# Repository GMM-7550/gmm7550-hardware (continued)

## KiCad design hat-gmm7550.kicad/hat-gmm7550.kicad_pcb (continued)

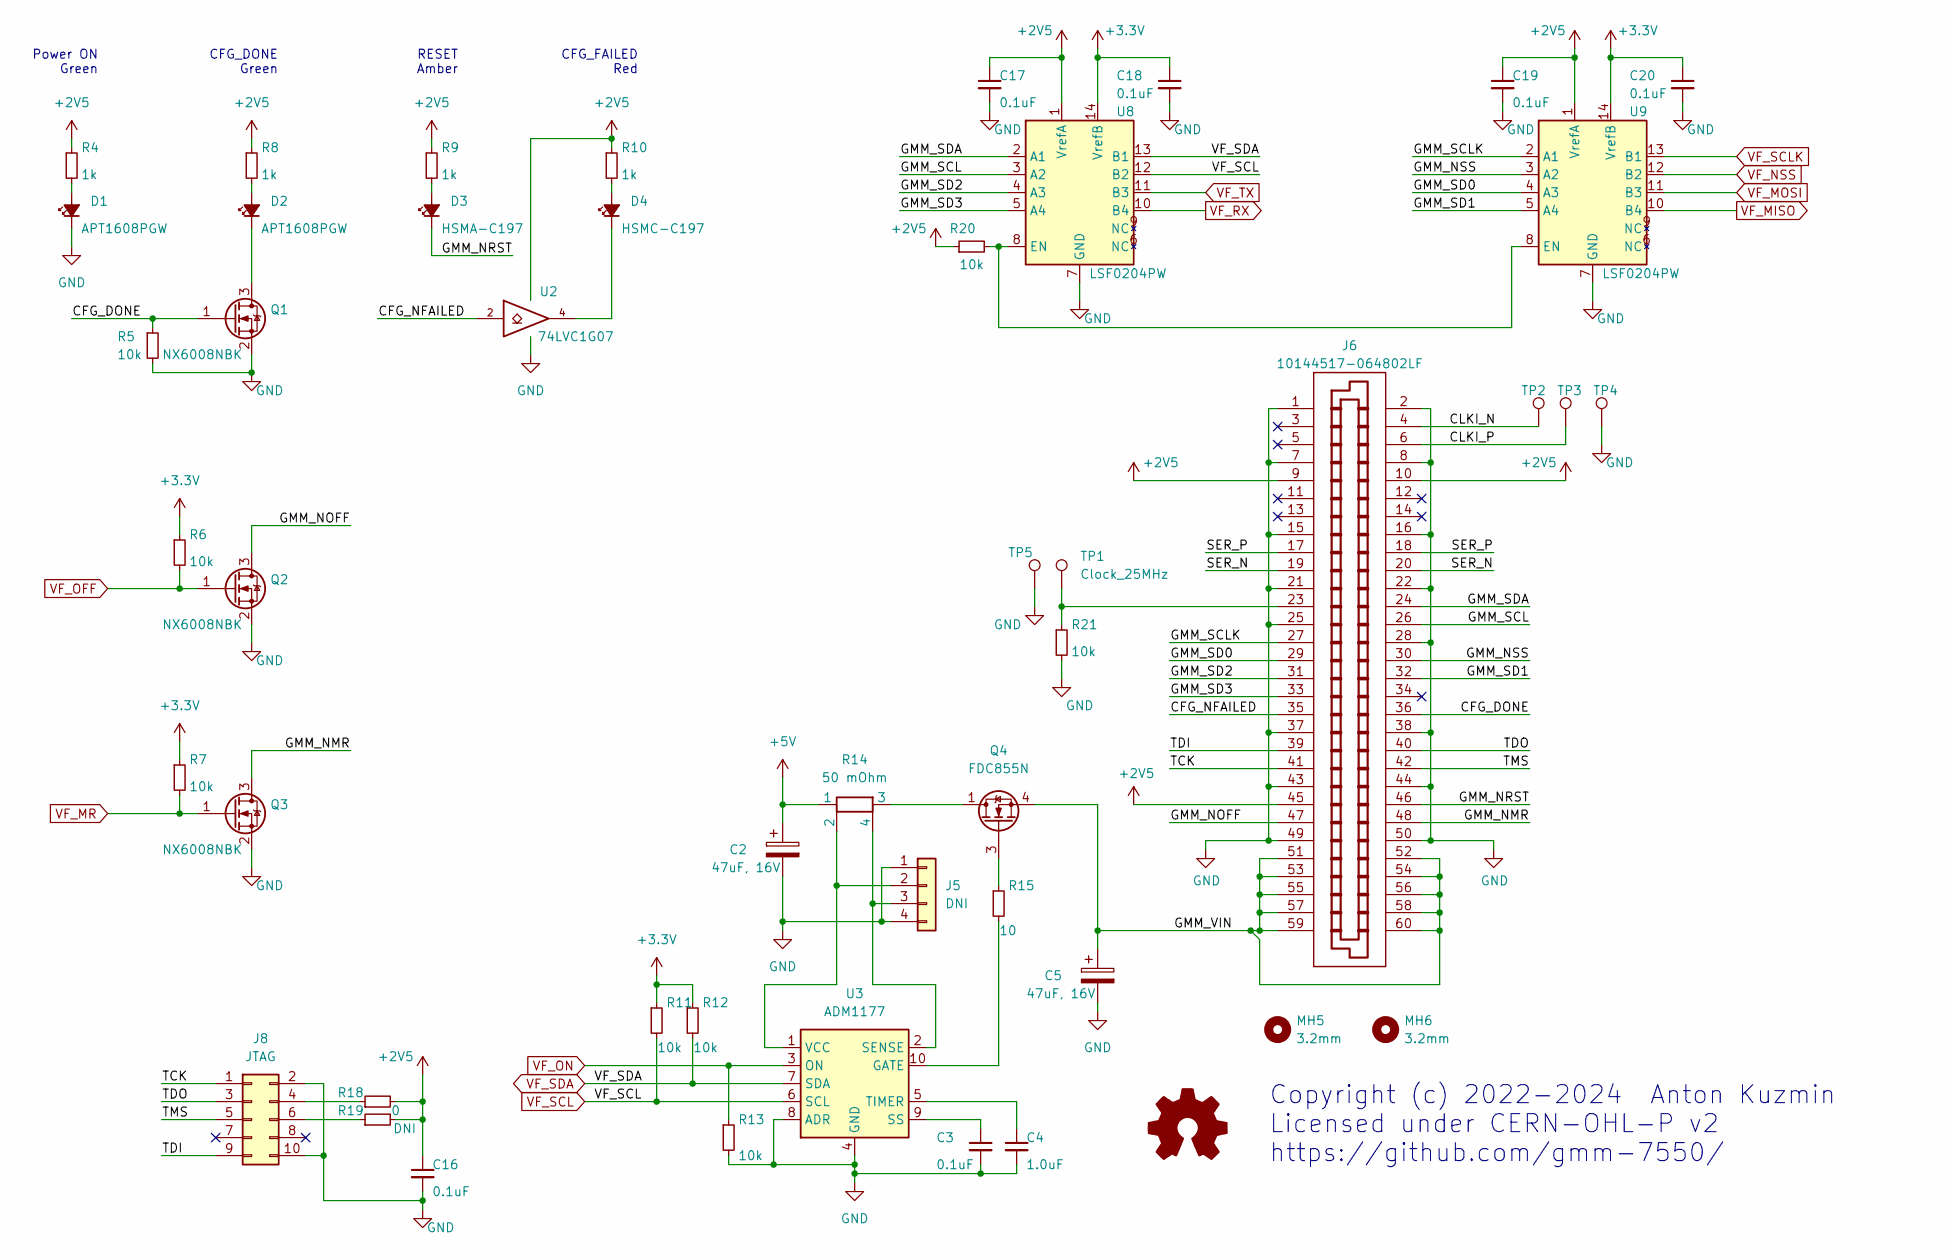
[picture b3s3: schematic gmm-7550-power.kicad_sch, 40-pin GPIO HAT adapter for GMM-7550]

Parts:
C2, C5: 47uF, 16V; CP_EIA-6032-28_Kemet-C; Part Number T491C476M016AT
C3, C16, C17, C18, C19, C20: 0.1uF; C_0603_1608Metric
C4: 1.0uF; C_0603_1608Metric
D1, D2: APT1608PGW; LED_0603_1608Metric
D3: HSMA-C197; LED_0603_1608Metric
D4: HSMC-C197; LED_0603_1608Metric
J5: DNI; PinHeader_1x04_P2.54mm_Vertical
J6: 10144517-064802LF; 10144517-061802LF
J8: JTAG; PinHeader_2x05_P2.54mm_Vertical
MH5, MH6: 3.2mm; MountingHole_3.2mm_M3_ISO7380
Q1, Q2, Q3: NX6008NBK; SOT-23
Q4: FDC855N; SuperSOT-6
R4, R8, R9, R10: 1k; R_0603_1608Metric
R5, R6, R7, R11, R12, R13, R20, R21: 10k; R_0603_1608Metric
R14: 50 mOhm; R_Shunt_Ohmite_LVK12; Part Number LVK12R050FER
R15: 10; R_0603_1608Metric
R18: 0; R_0603_1608Metric
R19: DNI; R_0603_1608Metric
TP1: Clock_25MHz; TestPoint_THTPad_D1.0mm_Drill0.5mm
TP2, TP3: Ref_CLK; TestPoint_THTPad_D1.0mm_Drill0.5mm
TP4, TP5: GND; TestPoint_THTPad_D1.0mm_Drill0.5mm
U2: 74LVC1G07; SOT-23-5
U3: ADM1177; MSOP-10_3x3mm_P0.5mm
U8, U9: LSF0204PW; TSSOP-14_4.4x5mm_P0.65mm

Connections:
+2V5: C16.1, C17.1, C19.1, J6.9, J6.10, J6.45, R4.1, R8.1, R9.1, R10.1, R18.2, R19.2, R20.1, U2.5 (VCC), U8.1 (VrefA), U9.1 (VrefA); also elsewhere on the board
+3V3: C18.1, C20.1, R6.1, R7.1, R11.1, R12.1, U8.14 (VrefB), U9.14 (VrefB); also elsewhere on the board
+5V: C2.1, R14.1; also elsewhere on the board
/GMM-7550 Power and Control/CFG_DONE: J6.36, Q1.1 (G), R5.1
/GMM-7550 Power and Control/CFG_NFAILED: J6.35, U2.2
/GMM-7550 Power and Control/CLKI_N: J6.4, TP2.1
/GMM-7550 Power and Control/CLKI_P: J6.6, TP3.1
/GMM-7550 Power and Control/GMM_NMR: J6.48, Q3.3 (D)
/GMM-7550 Power and Control/GMM_NOFF: J6.47, Q2.3 (D)
/GMM-7550 Power and Control/GMM_NRST: D3.1 (K), J6.46
/GMM-7550 Power and Control/GMM_NSS: J6.30, U9.3 (A2)
/GMM-7550 Power and Control/GMM_SCL: J6.26, U8.3 (A2)
/GMM-7550 Power and Control/GMM_SCLK: J6.27, U9.2 (A1)
/GMM-7550 Power and Control/GMM_SD0: J6.29, U9.4 (A3)
/GMM-7550 Power and Control/GMM_SD1: J6.32, U9.5 (A4)
/GMM-7550 Power and Control/GMM_SD2: J6.31, U8.4 (A3)
/GMM-7550 Power and Control/GMM_SD3: J6.33, U8.5 (A4)
/GMM-7550 Power and Control/GMM_SDA: J6.24, U8.2 (A1)
/GMM-7550 Power and Control/GMM_VIN: C5.1, J6.51, J6.52, J6.53, J6.54, J6.55, J6.56, J6.57, J6.58, J6.59, J6.60, Q4.4 (S)
/GMM-7550 Power and Control/SER_N: J6.19, J6.20
/GMM-7550 Power and Control/SER_P: J6.17, J6.18
/GMM-7550 Power and Control/TCK: J6.41, J8.1
/GMM-7550 Power and Control/TDI: J6.39, J8.9
/GMM-7550 Power and Control/TDO: J6.40, J8.3
/GMM-7550 Power and Control/TMS: J6.42, J8.5
GND: C2.2, C3.2, C4.2, C5.2, C16.2, C17.2, C18.2, C19.2, C20.2, D1.1 (K), J5.1, J5.4, J6.1, J6.2, J6.7, J6.8, J6.15, J6.16, J6.21, J6.22, J6.25, J6.28, J6.37, J6.38, J6.43, J6.44, J6.49, J6.50, J8.2, J8.10, Q1.2 (S), Q2.2 (S), Q3.2 (S), R5.2, R13.2, R21.2, TP4.1, TP5.1, U2.3 (GND), U3.4 (GND), U3.8 (ADR), U8.7 (GND), U9.7 (GND); also elsewhere on the board
unnamed: C3.1, U3.9 (SS)
unnamed: C4.1, U3.5 (TIMER)
unnamed: D1.2 (A), R4.2
unnamed: D2.1 (K), Q1.3 (D)
unnamed: D2.2 (A), R8.2
unnamed: D3.2 (A), R9.2
unnamed: D4.1 (K), U2.4
unnamed: D4.2 (A), R10.2
unnamed: J5.2, R14.2, U3.1 (VCC)
unnamed: J5.3, R14.4, U3.2 (SENSE)
unnamed: J6.23, R21.1, TP1.1
unnamed: J8.4, R18.1
unnamed: J8.6, R19.1
unnamed: Q4.1 (D), Q4.2 (D), Q4.5 (D), Q4.6 (D), R14.3
unnamed: Q4.3 (G), R15.1
unnamed: R15.2, U3.10 (GATE)
unnamed: R20.2, U8.8 (EN), U9.8 (EN)
VF_MISO: U9.10 (B4); also elsewhere on the board
VF_MOSI: U9.11 (B3); also elsewhere on the board
VF_MR: Q3.1 (G), R7.2; also elsewhere on the board
VF_NSS: U9.12 (B2); also elsewhere on the board
VF_OFF: Q2.1 (G), R6.2; also elsewhere on the board
VF_ON: R13.1, U3.3 (ON); also elsewhere on the board
VF_RX: U8.10 (B4); also elsewhere on the board
VF_SCL: R11.2, U3.6 (SCL), U8.12 (B2); also elsewhere on the board
VF_SCLK: U9.13 (B1); also elsewhere on the board
VF_SDA: R12.2, U3.7 (SDA), U8.13 (B1); also elsewhere on the board
VF_TX: U8.11 (B3); also elsewhere on the board

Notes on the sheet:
Power ON Green
Copyright (c) 2022-2024 Anton Kuzmin Licensed under CERN-OHL-P v2 https://github.com/gmm-7550/
CFG_FAILED Red
RESET Amber
CFG_DONE Green

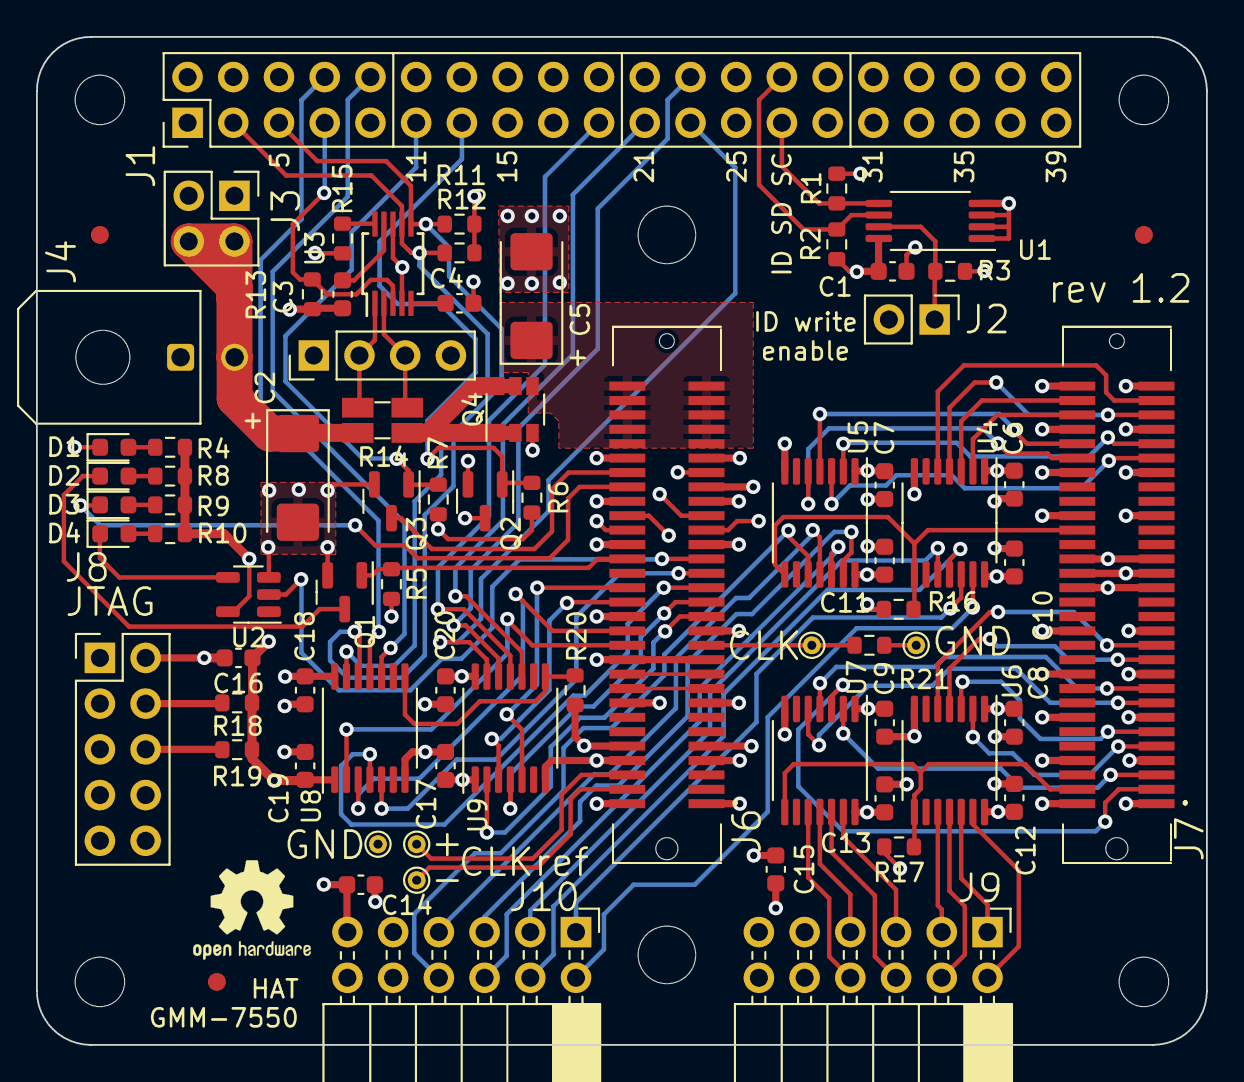
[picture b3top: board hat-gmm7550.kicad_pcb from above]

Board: 4 copper layers, 65.0 x 56.0 mm, 82 parts (0 on the bottom side), 92 nets.

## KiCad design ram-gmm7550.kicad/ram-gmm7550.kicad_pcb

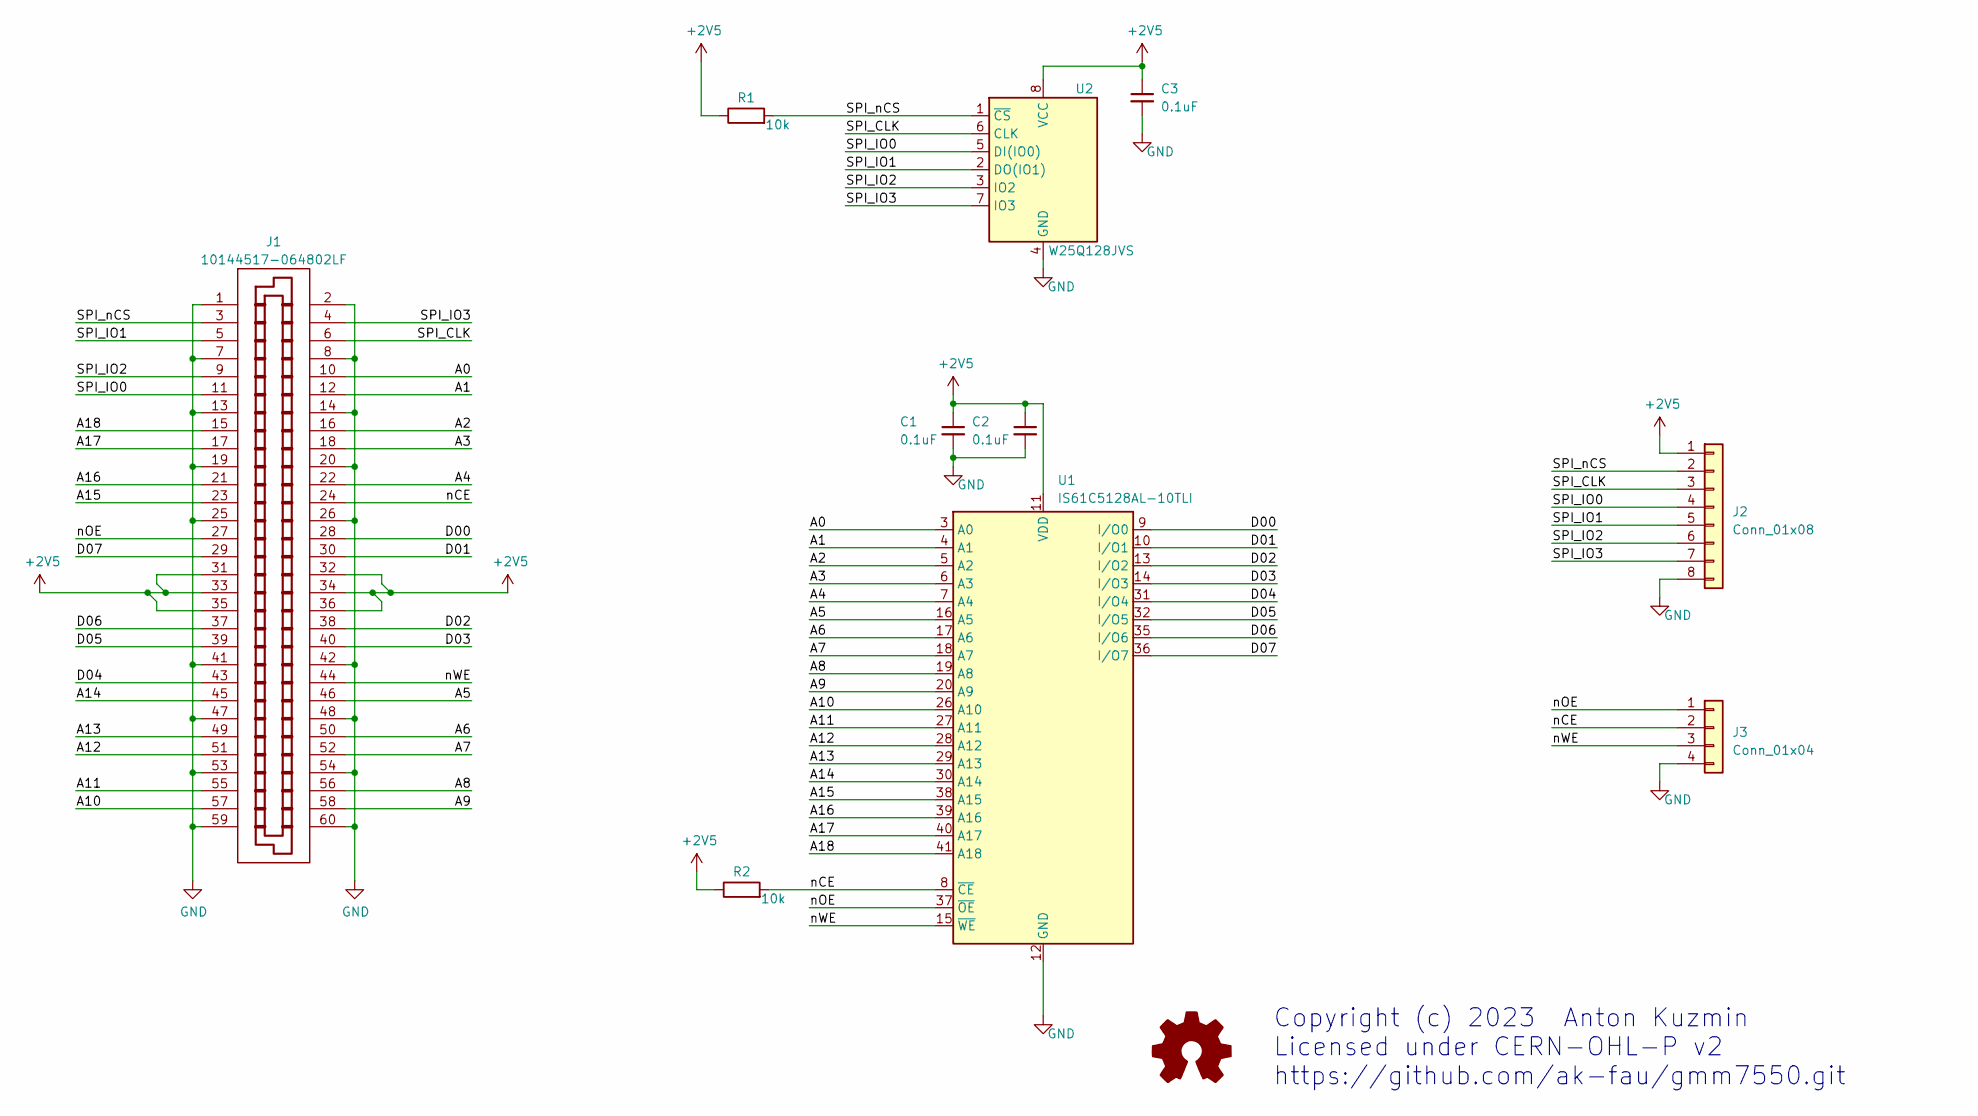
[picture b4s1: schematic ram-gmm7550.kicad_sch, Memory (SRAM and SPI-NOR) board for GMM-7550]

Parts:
C1, C2, C3: 0.1uF; C_0603_1608Metric
J1: 10144517-064802LF; 10144517-061802LF
J2: Conn_01x08; PinHeader_1x08_P2.54mm_Vertical
J3: Conn_01x04; PinHeader_1x04_P2.54mm_Vertical
R1, R2: 10k; R_0603_1608Metric
U1: IS61C5128AL-10TLI; TSOP-II-44_10.16x18.41mm_P0.8mm
U2: W25Q128JVS; SOIC-8_5.23x5.23mm_P1.27mm

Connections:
+2V5: C1.1, C2.1, C3.1, J1.31, J1.32, J1.33, J1.34, J1.35, J1.36, J2.1, R1.1, R2.1, U1.11 (VDD), U1.33 (VDD), U2.8 (VCC)
/A0: J1.10, U1.3 (A0)
/A1: J1.12, U1.4 (A1)
/A2: J1.16, U1.5 (A2)
/A3: J1.18, U1.6 (A3)
/A4: J1.22, U1.7 (A4)
/A5: J1.46, U1.16 (A5)
/A6: J1.50, U1.17 (A6)
/A7: J1.52, U1.18 (A7)
/A8: J1.56, U1.19 (A8)
/A9: J1.58, U1.20 (A9)
/A10: J1.57, U1.26 (A10)
/A11: J1.55, U1.27 (A11)
/A12: J1.51, U1.28 (A12)
/A13: J1.49, U1.29 (A13)
/A14: J1.45, U1.30 (A14)
/A15: J1.23, U1.38 (A15)
/A16: J1.21, U1.39 (A16)
/A17: J1.17, U1.40 (A17)
/A18: J1.15, U1.41 (A18)
/D00: J1.28, U1.9 (I/O0)
/D01: J1.30, U1.10 (I/O1)
/D02: J1.38, U1.13 (I/O2)
/D03: J1.40, U1.14 (I/O3)
/D04: J1.43, U1.31 (I/O4)
/D05: J1.39, U1.32 (I/O5)
/D06: J1.37, U1.35 (I/O6)
/D07: J1.29, U1.36 (I/O7)
/SPI_CLK: J1.6, J2.3, U2.6 (CLK)
/SPI_IO0: J1.11, J2.4, U2.5 (DI(IO0))
/SPI_IO1: J1.5, J2.5, U2.2 (DO(IO1))
/SPI_IO2: J1.9, J2.6, U2.3 (IO2)
/SPI_IO3: J1.4, J2.7, U2.7 (IO3)
/SPI_nCS: J1.3, J2.2, R1.2, U2.1 (~CS)
/nCE: J1.24, J3.2, R2.2, U1.8 (~CE)
/nOE: J1.27, J3.1, U1.37 (~OE)
/nWE: J1.44, J3.3, U1.15 (~WE)
GND: C1.2, C2.2, C3.2, J1.1, J1.2, J1.7, J1.8, J1.13, J1.14, J1.19, J1.20, J1.25, J1.26, J1.41, J1.42, J1.47, J1.48, J1.53, J1.54, J1.59, J1.60, J2.8, J3.4, U1.12 (GND), U1.34 (GND), U2.4 (GND)

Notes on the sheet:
Copyright (c) 2023 Anton Kuzmin Licensed under CERN-OHL-P v2 https://github.com/ak-fau/gmm7550.git

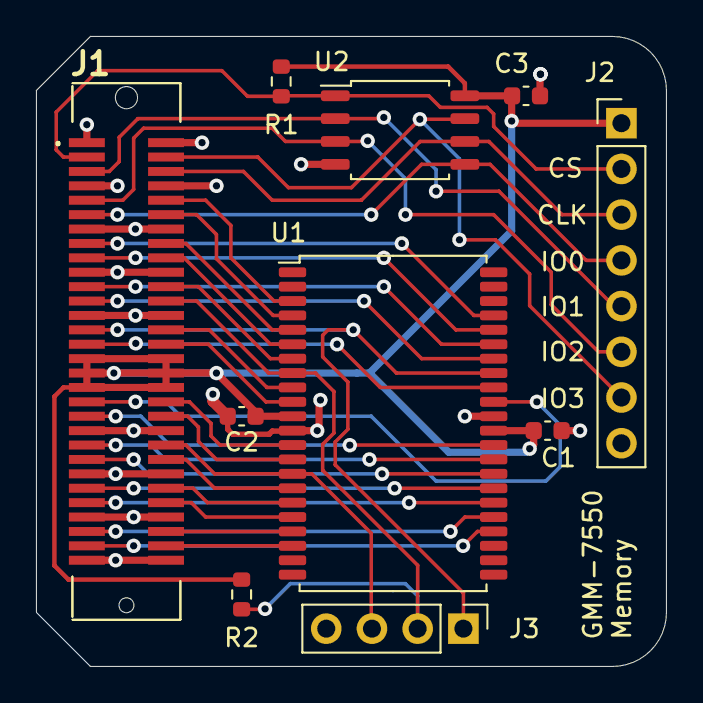
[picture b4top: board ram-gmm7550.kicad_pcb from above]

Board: 2 copper layers, 35.0 x 35.0 mm, 10 parts (0 on the bottom side), 38 nets.

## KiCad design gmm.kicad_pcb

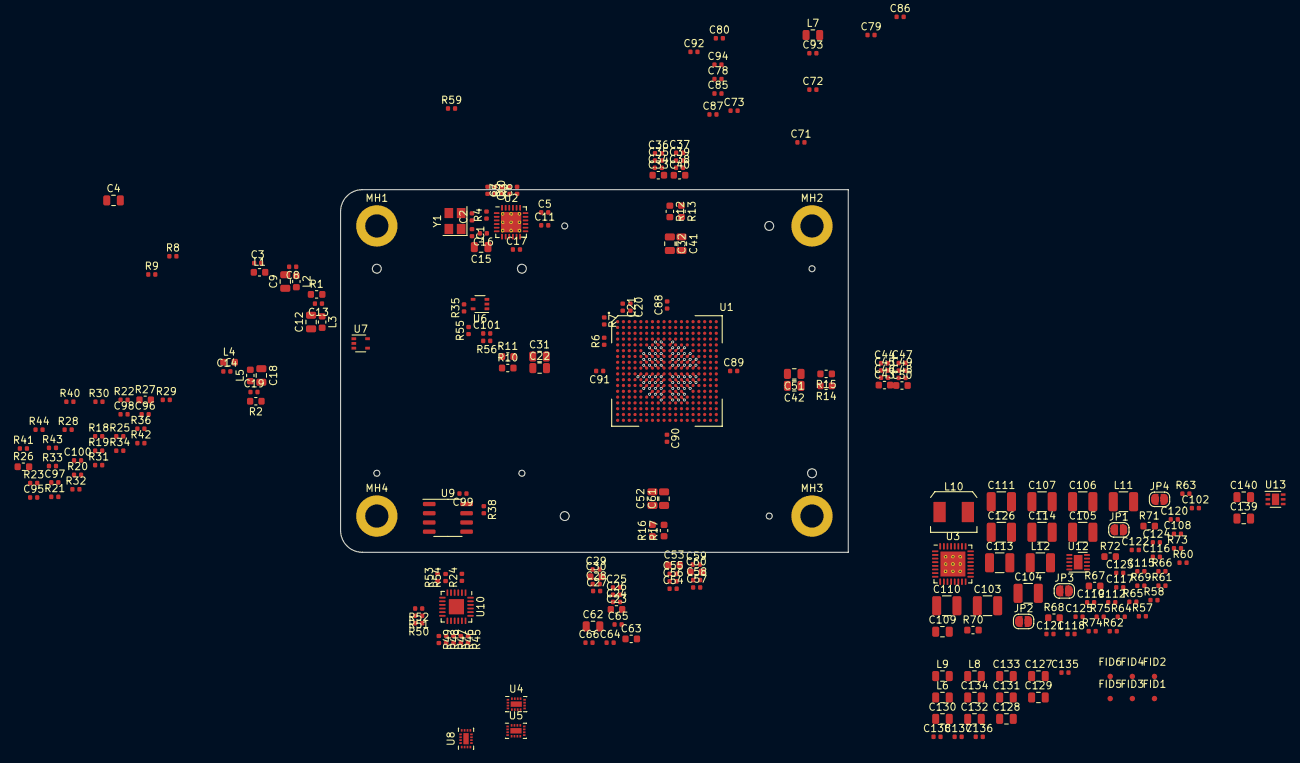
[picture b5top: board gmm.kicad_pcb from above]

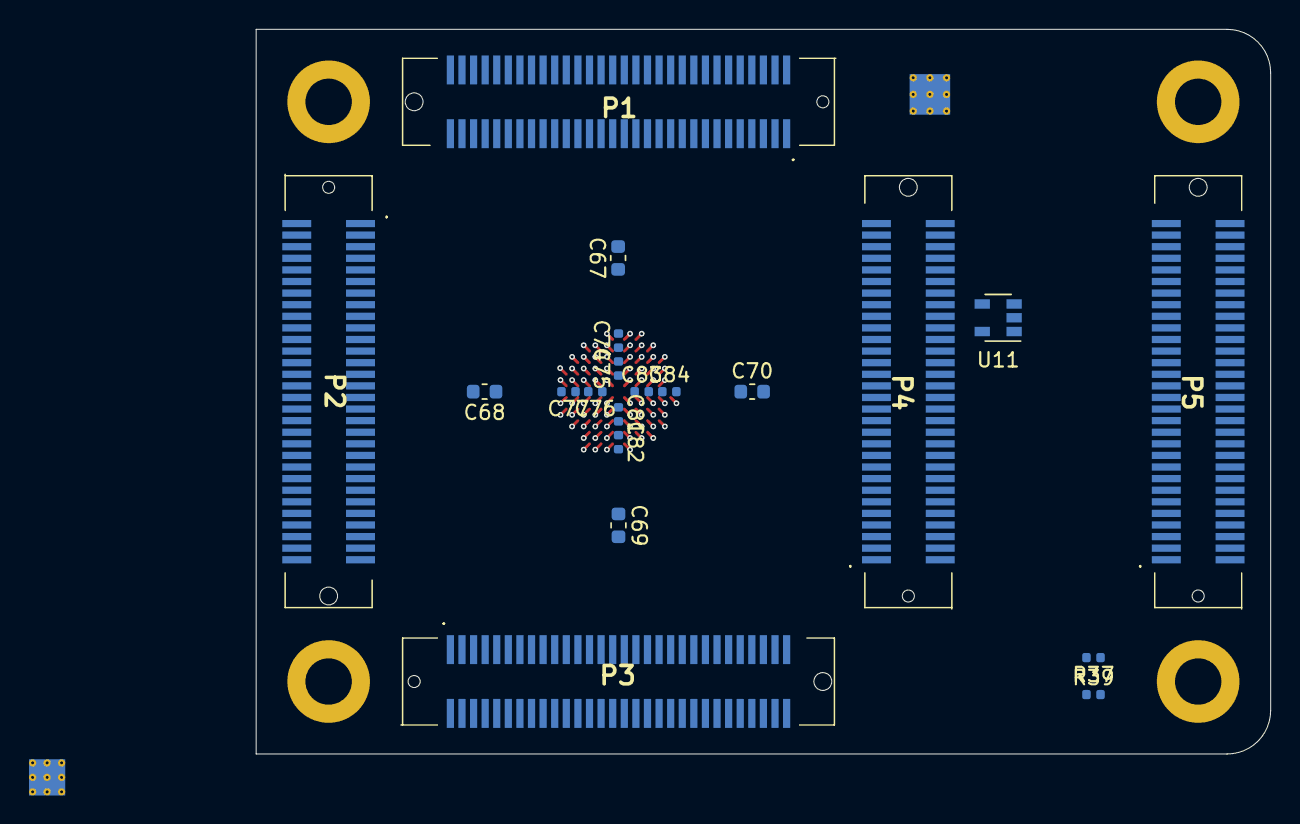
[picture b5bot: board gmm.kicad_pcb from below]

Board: 6 copper layers, 70.0 x 50.0 mm, 260 parts (20 on the bottom side), 259 nets.

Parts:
C1, C2, C118, C120, C123: DNI; C_0402_1005Metric
C3, C5, C6, C7, C8, C10, C11, C13, C14, C16, C17, C19, C20, C21, C24, C25, C26, C27, C28, C29, C34, C35, C36, C37, C38, C39, C44, C45, C46, C47, C48, C49, C54, C55, C56, C57, C58, C59, C64, C65, C66, C71, C72, C74, C75, C78, C79, C81, C82, C85, C86, C88, C89, C92, C93, C95, C96, C97, C98, C99, C100, C101, C125, C135, C136: 0.1uF; C_0402_1005Metric
C4, C9, C12, C15, C18, C22, C31, C32, C41, C42, C51, C52, C61, C62, C109, C127, C128, C129, C130, C131, C132, C133, C134, C139, C140: 2.2uF; C_0805_2012Metric
C23, C30, C33, C40, C43, C50, C53, C60, C63, C67, C68, C69, C70: 0.47uF; C_0603_1608Metric
C73, C76, C77, C80, C83, C84, C87, C90, C91, C94, C115, C116, C117, C122, C137, C138: 0.01uF; C_0402_1005Metric
C102, C108, C112: 0.047uF; C_0402_1005Metric
C103, C104, C105, C106, C107, C110, C111, C113, C114, C126: 22uF; C_1210_3225Metric
C119, C121, C124: 1000pF; C_0402_1005Metric
FID1, FID2, FID3, FID4, FID5, FID6: Fiducial; Fiducial_0.75mm_Mask1.5mm
JP1, JP2, JP3, JP4: SolderJumper_2_Open_Small; SolderJumper-2_P1.3mm_Open_RoundedPad1.0x1.5mm
L1, L2, L3, L4, L5: 4.7uH; L_0603_1608Metric
L6, L7, L8, L9: 600 Ohm @100MHz, 1.5A; L_0805_2012Metric
L10: 2.2uH; L_Murata_FDSD0518_5.2x4.9mm
L11, L12: 2.2uH; L_1210_3225Metric
MH1, MH2, MH3, MH4: MountingHole_Pad; MountingHole_3.2mm_M3_ISO7380_Pad
P1, P2, P3, P4, P5: 10144518-061802LF
R1, R2, R10, R11, R12, R13, R14, R15, R16, R17, R26, R27, R71: DNI; R_0603_1608Metric
R3, R22, R25, R29, R31, R32, R34, R36, R42: 33; R_0402_1005Metric
R4: 100; R_0402_1005Metric
R5, R8, R9, R18, R20, R21, R24, R35, R37, R38, R39, R40, R41, R45, R46, R47, R48, R49, R50, R51, R52, R53, R54, R55, R56, R59, R65, R66: 10k; R_0402_1005Metric
R6: DNI; R_0402_1005Metric
R7: 200; R_0402_1005Metric
R19, R28, R30, R33, R43, R44: 100k; R_0402_1005Metric
R23: 1k; R_0402_1005Metric
R57, R58: 2.49k; R_0402_1005Metric
R60: 23.7k; R_0402_1005Metric
R61, R62: 7.5k; R_0402_1005Metric
R63, R64: 15k; R_0402_1005Metric
R67: 10k; R_0603_1608Metric
R68, R72: 20k; R_0603_1608Metric
R69, R73, R74: 2k; R_0402_1005Metric
R70: 0; R_0603_1608Metric
R75: 16k; R_0402_1005Metric
U1: CCGM1A1; BGA-320_15.0x15.0mm_Layout18x18_P0.8mm
U2: 5P49V6965; QFN-24-1EP_4x4mm_P0.5mm_EP2.8x2.8mm_ThermalVias
U3: TPS65266; Texas_S-PVQFN-N32_EP3.45x3.45mm_ThermalVias
U4, U5, U8: STG3692; QFN-16-1EP_2.6x1.8mm_P0.4mm_EP1.5x0.7mm
U6: 74LVC1G08; SOT-353_SC-70-5
U7: 74LVC1G07; SOT-353_SC-70-5
U9: IS25LQ032B-JNLE; SO-8_3.9x4.9mm_P1.27mm
U10: PCA9539AHF; Texas_S-PVQFN-N24_EP2.1x2.1mm
U11: TPS3840DL28DBV; SOT-23-5
U12: TPS7A91; Texas_S-PDSO-N10_EP1.2x2mm
U13: ADP151ACP; DFN-6-1EP_2x2mm_P0.65mm_EP1x1.6mm
Y1: NX3225SA; Crystal_SMD_3225-4Pin_3.2x2.5mm

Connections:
+1V0: C67.1, C68.1, C69.1, C70.1, C74.1, C75.1, C76.1, C77.1, C81.1, C82.1, C83.1, C84.1, C88.1, C89.1, C90.1, C91.1, C106.1, C107.1, C128.1, C129.1, C130.1, C131.1, C135.1, C136.1, C137.1, C138.1, JP1.1, L10.2, R57.1, U1.F10, U1.G7, U1.G9, U1.G11, U1.H8, U1.H10, U1.H12, U1.J7, U1.J9, U1.J11, U1.J13, U1.K6, U1.K8, U1.K10, U1.K12, U1.L7, U1.L9, U1.L11, U1.M8, U1.M10, U1.M12, U1.N9
+2V5: C3.1, C62.1, C63.1, C64.1, C65.1, C66.1, C92.1, C95.1, C96.1, C98.1, C99.1, C100.1, C110.1, C111.1, C134.1, C139.1, L1.1, L9.2, L11.2, P1.33, P1.34, P2.33, P2.34, P3.33, P3.34, P4.33, P4.34, R1.1, R2.1, R10.1, R11.1, R12.1, R13.1, R14.1, R15.1, R16.1, R17.1, R18.1, R19.1, R20.1, R21.1, R24.2, R35.1, R37.1, R38.1, R39.1, R40.1, R41.1, R56.1, R60.1, U1.N7, U1.P8, U1.R6, U1.U3, U1.U6, U4.2, U5.2, U6.5, U7.5, U8.2, U9.8, U10.21, U13.4, U13.6
/Clock and SERDES/CLK_N: R6.1, U1.E1, U2.19
/Clock and SERDES/CLK_P: R6.2, U1.D2, U2.20
/Clock and SERDES/TXC_N: C21.2, U1.A2
/Clock and SERDES/TXC_P: C20.2, U1.A3
/Clock and SERDES/VDD_PLL: C8.1, C14.1, C140.1, L2.1, L4.1, U13.1
/Clock and SERDES/XIN: C1.1, U2.4, Y1.1
/Clock and SERDES/XOUT: C2.1, U2.3, Y1.3
/Configuration and Control/CFG_MD0: R52.1, U1.T3, U10.10
/Configuration and Control/CFG_MD1: R51.1, U1.T4, U10.11
/Configuration and Control/CFG_MD2: R50.1, U1.U1, U10.12
/Configuration and Control/CFG_MD3: R49.1, U1.U2, U10.13
/Configuration and Control/GM_SPI_CLK: U1.U8, U4.13
/Configuration and Control/GM_SPI_CS_N: U1.V8, U4.8
/Configuration and Control/GM_SPI_D0: U1.T8, U4.16
/Configuration and Control/GM_SPI_D1: U1.R8, U4.5
/Configuration and Control/GM_SPI_D2: U1.U7, U8.16
/Configuration and Control/GM_SPI_D3: U1.V7, U8.5
/Configuration and Control/NOR_CLK: U5.13, U9.6
/Configuration and Control/NOR_CS_N: R37.2, U5.8, U9.1
/Configuration and Control/NOR_D0: U5.16, U9.5
/Configuration and Control/NOR_D1: U5.5, U9.2
/Configuration and Control/NOR_D2: R39.2, U8.13, U9.3
/Configuration and Control/NOR_D3: R38.2, U8.8, U9.7
/Configuration and Control/POR_EN: R24.1, U1.V4, U10.2
/Configuration and Control/RFU0: R54.1, U10.5
/Configuration and Control/RFU1: R53.1, U10.6
/Configuration and Control/SPI_SEL0: R48.1, U4.3, U4.10, U10.14
/Configuration and Control/SPI_SEL1: R47.1, U5.3, U5.10, U10.15
/Configuration and Control/SPI_SEL2: R46.1, U8.3, U10.16
/Configuration and Control/SPI_SEL3: R45.1, U8.10, U10.17
/Power Converter/COMP1: C118.2, R67.2, U3.23
/Power Converter/COMP2: C120.2, R68.2, U3.7
/Power Converter/COMP3: C123.2, R72.2, U3.18
/Power Converter/V_1P5: C113.1, C114.1, L12.2, R64.1, R70.2, U12.7, U12.9, U12.10
CFG_DONE: U1.V3, U10.8
CFG_FAILED_N: R18.2, U1.V2, U10.7
CLKI_N: R4.1, U2.2
CLKI_P: R4.2, U2.1
CLKSDOE: R9.2, U2.7, U10.4
CLKSEL: R8.2, U2.6, U10.3
GND: C1.2, C2.2, C3.2, C4.2, C5.2, C6.2, C7.2, C8.2, C9.2, C10.2, C11.2, C12.2, C13.2, C14.2, C15.2, C16.2, C17.2, C18.2, C19.2, C22.2, C23.2, C24.2, C25.2, C26.2, C27.2, C28.2, C29.2, C30.2, C31.2, C32.2, C33.2, C34.2, C35.2, C36.2, C37.2, C38.2, C39.2, C40.2, C41.2, C42.2, C43.2, C44.2, C45.2, C46.2, C47.2, C48.2, C49.2, C50.2, C51.2, C52.2, C53.2, C54.2, C55.2, C56.2, C57.2, C58.2, C59.2, C60.2, C61.2, C62.2, C63.2, C64.2, C65.2, C66.2, C67.2, C68.2, C69.2, C70.2, C71.2, C72.2, C73.2, C74.2, C75.2, C76.2, C77.2, C78.2, C79.2, C80.2, C81.2, C82.2, C83.2, C84.2, C85.2, C86.2, C87.2, C88.2, C89.2, C90.2, C91.2, C92.2, C93.2, C94.2, C95.2, C96.2, C97.2, C98.2, C99.2, C100.2, C101.2, C103.2, C104.2, C105.2, C106.2, C107.2, C109.2, C110.2, C111.2, C113.2, C114.2, C115.2, C116.2, C117.2, C118.1, C119.1, C120.1, C121.1, C123.1, C124.1, C125.2, C126.2, C127.2, C128.2, C129.2, C130.2, C131.2, C132.2, C133.2, C134.2, C135.2, C136.2, C137.2, C138.2, C139.2, C140.2, MH1.1, MH2.1, MH3.1, MH4.1, P1.1, P1.2, P1.7, P1.8, P1.13, P1.14, P1.19, P1.20, P1.25, P1.26, P1.41, P1.42, P1.47, P1.48, P1.53, P1.54, P1.59, P1.60, P2.1, P2.2, P2.7, P2.8, P2.13, P2.14, P2.19, P2.20, P2.25, P2.26, P2.41, P2.42, P2.47, P2.48, P2.53, P2.54, P2.59, P2.60, P3.1, P3.2, P3.7, P3.8, P3.13, P3.14, P3.19, P3.20, P3.25, P3.26, P3.41, P3.42, P3.47, P3.48, P3.53, P3.54, P3.59, P3.60, P4.1, P4.2, P4.7, P4.8, P4.13, P4.14, P4.19, P4.20, P4.25, P4.26, P4.41, P4.42, P4.47, P4.48, P4.53, P4.54, P4.59, P4.60, R5.1, R7.1, R8.1, R9.1, R23.1, R27.2, R28.2, R30.2, R33.2, R43.1, R44.1, R45.2, R46.2, R47.2, R48.2, R49.2, R50.2, R51.2, R52.2, R53.2, R54.2, R62.2, R63.2, R65.2, R66.2, R71.2, R75.2, U1.A1, U1.A4, U1.A12, U1.A18, U1.B7, U1.B16, U1.C12, U1.D1, U1.D3, U1.D6, U1.D16, U1.E2, U1.E3, U1.E6, U1.E8, U1.E10, U1.E12, U1.E13, U1.E15, U1.E17, U1.F5, U1.F7, U1.F9, U1.F11, U1.F14, U1.G6, U1.G8, U1.G10, U1.G12, U1.H1, U1.H3, U1.H5, U1.H7, U1.H9, U1.H11, U1.H13, U1.H14, U1.J6, U1.J8, U1.J10, U1.J12, U1.K5, U1.K7, U1.K9, U1.K11, U1.K13, U1.K14, U1.K16, U1.K18, U1.L6, U1.L8, U1.L10, U1.L12, U1.L14, U1.M7, U1.M9, U1.M11, U1.N5, U1.N8, U1.N10, U1.N12, U1.P1, U1.P3, U1.P6, U1.P7, U1.P9, U1.P11, U1.P14, U1.R16, U1.R18, U1.T6, U1.T11, U1.U4, U1.U16, U1.V1, U1.V6, U1.V11, U1.V18, U2.25, U3.1, U3.2, U3.3, U3.11, U3.14, U3.21, U3.27, U3.32, U3.33, U4.11, U5.11, U6.3, U7.3, U8.11, U9.4, U10.9, U10.18, U10.23, U10.25, U11.3, U12.4, U12.11, U13.3, U13.7, Y1.2, Y1.4
IO_E1_A0: P2.58, U1.N15
IO_E1_A1: P2.57, U1.M15
IO_E1_A2: P2.52, U1.M18
IO_E1_A3: P2.51, U1.L15
IO_E1_A4: P2.46, U1.L18
IO_E1_A5: P2.45, U1.J15
IO_E1_A6: P2.40, U1.J18
IO_E1_A7: P2.39, U1.H15
IO_E1_A8: P2.30, U1.H18
IO_E1_B0: P2.56, U1.N16
IO_E1_B1: P2.55, U1.M16
IO_E1_B2: P2.50, U1.M17
IO_E1_B3: P2.49, U1.L16
IO_E1_B4: P2.44, U1.L17
IO_E1_B5: P2.43, U1.J16
IO_E1_B6: P2.38, U1.J17
IO_E1_B7: P2.37, U1.H16
IO_E1_B8: P2.28, U1.H17
IO_E2_A0: P2.29, U1.G15
IO_E2_A1: P2.22, U1.G18
IO_E2_A2: P2.23, U1.F15
IO_E2_A3: P2.18, U1.F18
IO_E2_A4: P2.17, U1.D18
IO_E2_A5: P2.12, U1.C16
IO_E2_A6: P2.11, U1.C18
IO_E2_A7: P2.6, U1.A17
IO_E2_A8: P2.5, U1.B15
IO_E2_B0: P2.27, U1.G16
IO_E2_B1: P2.24, U1.G17
IO_E2_B2: P2.21, U1.F16
IO_E2_B3: P2.16, U1.F17
IO_E2_B4: P2.15, U1.D17
IO_E2_B5: P2.10, U1.C17
IO_E2_B6: P2.9, U1.B18
IO_E2_B7: P2.4, U1.A16
IO_E2_B8: P2.3, U1.A15
IO_N1_A0: P1.4, U1.C4
IO_N1_A1: P1.3, U1.D5
IO_N1_A2: P1.10, U1.A5
IO_N1_A3: P1.9, U1.A6
IO_N1_A4: P1.16, U1.D7
IO_N1_A5: P1.15, U1.D8
IO_N1_A6: P1.22, U1.A8
IO_N1_A7: P1.21, U1.D9
IO_N1_A8: P1.28, U1.A9
IO_N1_B0: P1.6, U1.B4
IO_N1_B1: P1.5, U1.C5
IO_N1_B2: P1.12, U1.B5
IO_N1_B3: P1.11, U1.B6
IO_N1_B4: P1.18, U1.C7
IO_N1_B5: P1.17, U1.C8
IO_N1_B6: P1.24, U1.B8
IO_N1_B7: P1.23, U1.C9
IO_N1_B8: P1.30, U1.B9
IO_N2_A0: P1.29, U1.D10
IO_N2_A1: P1.40, U1.A10
IO_N2_A2: P1.39, U1.D11
IO_N2_A3: P1.46, U1.A11
IO_N2_A4: P1.45, U1.D13
IO_N2_A5: P1.52, U1.A13
IO_N2_A6: P1.51, U1.D14
IO_N2_A7: P1.58, U1.A14
IO_N2_A8: P1.57, U1.D15
IO_N2_B0: P1.27, U1.C10
IO_N2_B1: P1.38, U1.B10
IO_N2_B2: P1.37, U1.C11
IO_N2_B3: P1.44, U1.B11
IO_N2_B4: P1.43, U1.C13
IO_N2_B5: P1.50, U1.B13
IO_N2_B6: P1.49, U1.C14
IO_N2_B7: P1.56, U1.B14
IO_N2_B8: P1.55, U1.C15
IO_S1_A0: P3.57, U1.R9
IO_S1_A1: P3.58, U1.V9
IO_S1_A2: P3.51, U1.R10
IO_S1_A3: P3.52, U1.V10
IO_S1_A4: P3.45, U1.R12
IO_S1_A5: P3.46, U1.V12
IO_S1_A6: P3.37, U1.R13
IO_S1_A7: P3.40, U1.V13
IO_S1_A8: P3.30, U1.V14
IO_S1_B0: P3.55, U1.T9
IO_S1_B1: P3.56, U1.U9
IO_S1_B2: P3.49, U1.T10
IO_S1_B3: P3.50, U1.U10
IO_S1_B4: P3.43, U1.T12
IO_S1_B5: P3.44, U1.U12
IO_S1_B6: P3.39, U1.T13
IO_S1_B7: P3.38, U1.U13
IO_S1_B8: P3.28, U1.U14
IO_S2_A0: P3.23, U1.R14
IO_S2_A1: P3.29, U1.V15
IO_S2_A2: P3.17, U1.R15
IO_S2_A3: P3.22, U1.V16
IO_S2_A4: P3.11, U1.T16
IO_S2_A5: P3.16, U1.U18
IO_S2_A6: P3.5, U1.P15
IO_S2_A7: P3.10, U1.P18
IO_S2_A8: P3.4, U1.N18
IO_S2_B0: P3.21, U1.T14
IO_S2_B1: P3.27, U1.U15
IO_S2_B2: P3.15, U1.T15
IO_S2_B3: P3.24, U1.V17
IO_S2_B4: P3.9, U1.T17
IO_S2_B5: P3.18, U1.T18
IO_S2_B6: P3.3, U1.P16
IO_S2_B7: P3.12, U1.P17
IO_S2_B8: P3.6, U1.N17
IO_W1_A0: P4.4, U1.T2
IO_W1_A1: P4.5, U1.R4
IO_W1_A2: P4.10, U1.R2
IO_W1_A3: P4.11, U1.R5
IO_W1_A4: P4.17, U1.N3
IO_W1_A5: P4.16, U1.N2
IO_W1_A6: P4.23, U1.M3
IO_W1_A7: P4.22, U1.M2
IO_W1_A8: P4.29, U1.L3
IO_W1_B0: P4.6, U1.T1
IO_W1_B1: P4.3, U1.R3
IO_W1_B2: P4.12, U1.R1
IO_W1_B3: P4.9, U1.P5
IO_W1_B4: P4.15, U1.N4
IO_W1_B5: P4.18, U1.N1
IO_W1_B6: P4.21, U1.M4
IO_W1_B7: P4.24, U1.M1
IO_W1_B8: P4.27, U1.L4
IO_W2_A0: P4.28, U1.L2
IO_W2_A1: P4.40, U1.K2
IO_W2_A2: P4.39, U1.K3
IO_W2_A3: P4.46, U1.J2
IO_W2_A4: P4.45, U1.J3
IO_W2_A5: P4.52, U1.G2
IO_W2_A6: P4.51, U1.G3
IO_W2_A7: P4.58, U1.F2
IO_W2_A8: P4.57, U1.F3
IO_W2_B0: P4.30, U1.L1
IO_W2_B1: P4.38, U1.K1
IO_W2_B2: P4.37, U1.K4
IO_W2_B3: P4.44, U1.J1
IO_W2_B4: P4.43, U1.J4
IO_W2_B5: P4.50, U1.G1
IO_W2_B6: P4.49, U1.G4
IO_W2_B7: P4.56, U1.F1
IO_W2_B8: P4.55, U1.F4
JTAG_TCK: R23.2, U1.R7
JTAG_TDI: R21.2, U1.T5
JTAG_TMS: R20.2, U1.U5
MR_N: R55.2, U11.4
unnamed: C4.1, C5.1, C6.1, C7.1, L1.2, U2.18, U2.21, U2.23
unnamed: C9.1, C10.1, L2.2, U2.22
unnamed: C11.1, C12.1, L3.2, U2.15
unnamed: C15.1, C16.1, L4.2, U2.5
unnamed: C17.1, C18.1, L5.2, U2.10
unnamed: C72.1, C73.1, L6.2, U1.B3
unnamed: C79.1, C80.1, L7.2, U1.C2
unnamed: C86.1, C87.1, L8.2, U1.E5
unnamed: C97.1, R26.1, R27.1, U1.C3
unnamed: C101.1, U11.5
unnamed: C102.1, L10.1, U3.26
unnamed: C102.2, U3.25
unnamed: C108.1, L11.1, U3.10
unnamed: C108.2, U3.9
unnamed: C112.1, L12.1, U3.15
unnamed: C112.2, U3.16
unnamed: C115.1, U3.24
unnamed: C116.1, U3.8
unnamed: C117.1, U3.17
unnamed: C119.2, R67.1
unnamed: C121.2, R68.1
unnamed: C122.2, R74.2, R75.1, U12.3
unnamed: C124.2, R72.1
unnamed: C125.1, U12.8
unnamed: JP1.2, JP2.1, R57.2, R58.1
unnamed: JP2.2, R58.2, R61.1
unnamed: JP3.2, JP4.1, R69.2, R73.1
unnamed: JP4.2, R73.2, R74.1
unnamed: R3.2, R5.2, U2.24
unnamed: R7.2, U1.B2
unnamed: R19.2, R32.2, U4.7, U5.7
unnamed: R22.1, U1.V5
unnamed: R25.2, U1.T7
unnamed: R28.1, R29.2, U4.15, U5.15
unnamed: R30.1, R31.2, U4.4, U5.4
unnamed: R33.1, R34.2, U4.12, U5.12
unnamed: R35.2, U6.2, U10.1
unnamed: R36.2, R44.2, U8.12, U8.15
unnamed: R42.2, R43.2, U8.4, U8.7
unnamed: R60.2, R62.1, U3.6
unnamed: R61.2, R63.1, U3.22
unnamed: R64.2, R66.1, U3.19
unnamed: R65.1, U3.20
unnamed: R70.1, R71.1, U12.6
unnamed: U1.D4, U6.4, U7.2
unnamed: U4.1, U5.1
unnamed: U4.6, U5.6
unnamed: U4.9, U5.9
unnamed: U4.14, U5.14
unnamed: U8.1, U8.14
unnamed: U8.6, U8.9
OFF_N: R59.2, U3.29, U3.30, U3.31
POR_N: R56.2, U3.4, U6.1, U10.24, U11.1, U12.5
SCL: R40.2, U2.9, U10.19
SDA: R41.2, U2.8, U10.20
VCLKO3: C13.1, L3.1, R1.2
VCLKO4: C19.1, L5.1, R2.2
VDD_CLK: C93.1, C94.1, L9.1, R26.2, U1.E4
VIO_E1: C42.1, C43.1, C44.1, C45.1, C46.1, P2.35, P2.36, R14.2, U1.J14, U1.K15, U1.K17, U1.L13, U1.M14
VIO_E2: C47.1, C48.1, C49.1, C50.1, C51.1, P2.31, P2.32, R15.2, U1.B17, U1.E16, U1.E18, U1.G13, U1.G14
VIO_N1: C32.1, C33.1, C34.1, C35.1, C36.1, P1.31, P1.32, R12.2, U1.A7, U1.C6, U1.E7, U1.E9, U1.F8
VIO_N2: C37.1, C38.1, C39.1, C40.1, C41.1, P1.35, P1.36, R13.2, U1.B12, U1.D12, U1.E11, U1.E14, U1.F12
VIO_S1: C52.1, C53.1, C54.1, C55.1, C56.1, P3.35, P3.36, R16.2, U1.N11, U1.P10, U1.P12, U1.R11, U1.U11
VIO_S2: C57.1, C58.1, C59.1, C60.1, C61.1, P3.31, P3.32, R17.2, U1.M13, U1.N14, U1.P13, U1.R17, U1.U17
VIO_W1: C22.1, C23.1, C24.1, C25.1, C26.1, P4.31, P4.32, R10.2, U1.L5, U1.M5, U1.M6, U1.P2, U1.P4
VIO_W2: C27.1, C28.1, C29.1, C30.1, C31.1, P4.35, P4.36, R11.2, U1.G5, U1.H2, U1.H4, U1.H6, U1.J5
V_1P0_A: C71.1, C78.1, C85.1, C122.1, C126.1, C127.1, C132.1, C133.1, JP3.1, L6.1, L7.1, L8.1, R69.1, U12.1, U12.2
V_IN: C103.1, C104.1, C105.1, C109.1, R55.1, R59.1, U3.5, U3.12, U3.13, U3.28, U11.2

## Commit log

2020-04-01 GateMate Module -- first step
2020-04-02 FPGA core and IO power, PLL and SERDES, FPGA GPIO signals are connected... WIP
2020-04-08 Schematic is [almost] done. TODO: Connectors and a few footprints
2020-04-08 Footprint for high bandwidth quad SPDT switch (STmicro STG3692) is created.
2020-05-20 Switch to five identical connectors, draft IO connection, current working PCB size is 50 x 75 mm
2020-06-03 BOM clean-up: unified R/C values and footprints
2020-06-03 Add missing connection
2020-06-03 Placement and a bit of FPGA fanout
2020-06-03 Placement -- WIP
2020-07-08 Redesing power tree.
2020-07-08 CologneChip logo is added to all schematic pages
2020-07-08 Change power decoupling caps according to the Eval.Board schematic
2020-07-23 PLL core power from a low-noise LDO (1.8V)
2020-07-27 Clean-up/logo/copyright note
2020-07-27 Add footprints for solder jumpers and L10 inductor
2020-10-01 Schematic freeze, preliminary placement is done.
2020-10-01 Add copy of CERN-OHL-P v2 license
2020-10-01 Nice things for releasing the project on GitHub
2020-10-01 Clean-up project structure
2020-10-02 Add warning concerning preliminary pinout and required update.
    Based on the information from CologneChip technical support the pinout of the final chip will be different and the manufacturing of the module should be postponed. The estimated chips' availability d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
2022-03-16 The module design is updated to revision 2.0, 40-pin GPIO (HAT) adapter board is created
2022-04-19 DRC and cleanup HAT GMM-7550
2022-04-19 DRC and cleanup GMM-7550
2022-04-25 Change U2 footprint due to the part availability, revision and date are updated (HAT GMM-7550)
2022-04-25 HAT GMM-7550 -- add mounting holes positions to a mechanical drawing
2022-04-25 Change U7 footprint due to the part availability, revision and date are updated, DRC warnings clean-up (GMM-7550)
2022-04-25 Update schematic printouts (PDF)
2022-04-27 Add mounting holes to the User Drawing (GMM-7550)
2022-06-18 Update README with images of the assembled boards -- it's showtime!
2023-04-13 Small module with SRAM and SPI-NOR FLASH
2023-05-17 Add Memory extension module description, schematic, and photo.
2024-01-07 Add a note on the project relocation
2024-01-07 Change link to the new account (instead of the new repository)
2024-01-22 Update designs to KiCad v7
2024-01-22 Update copyright years and increment revision
2024-01-25 Minor updates based on the test results
2024-01-29 Update QR-code with a link to the project web site
2024-02-12 Change module connector part number: 9mm board-to-board distance
2025-05-31 Show more with 'git status'
2025-05-31 The first step of the USB 3 project -- adapter block diagram
2025-07-05 Add USB 1.1 Driver/Receiver implementation option
2025-07-12 Add pages to the USB 3 Adapter schematic and new project symbols
2025-07-12 Ignore [more] temporary files
2025-07-17 USB 3 adapter schematic -- WIP
2025-07-20 USB 3 adapter schematic -- WIP: new components and footprints
2025-07-22 USB 3 adapter schematic -- WIP: USB 3 and Power Delivery pages
2025-07-23 USB 3 adapter schematic -- WIP: USB 1.1 and 2.0 page, connections to the GMM-7550 IOs
2025-07-24 USB 3 adapter schematic: revision 0.9 (pre-layout) is ready
2025-07-24 Update README with a link to the USB 3 adapter schematic (revision 0.9, pre-layout)
2025-07-24 Fix typo in the USB 3 Adapter schematic pdf filename
2025-08-07 Placement: WIP, schematic update to 0.9.1 -- BoM simplification and minor improvements
2025-08-10 Change to smaller resistors
2025-08-10 Add missing 3D models
2025-08-10 Placement -- work in progress
2025-08-17 Change LED current limiting resistors to smaller package
2025-08-17 Change SPI NOR Flash (U14) to smaller package and wide Vcc range (for possible update to Vio=1.8V)
2025-08-17 Update schematic revision (0.9.2) and date
2025-08-17 Preliminary placement is ready
2025-08-17 Update README with 3D render of the USB 3 Adapter
2025-08-28 Connect USB 3 SuperSpeed diff. pairs
2025-08-29 Layout: break-out J1 (target USB Type-C)
2025-09-01 Layout -- suffling FPGA IOs (LEDs, buttons)
2025-09-02 Add USB Type-C plug polarity indication (A_B_SIDE signal from PD controller)
2025-09-16 Layout -- re-arrange and connect all GMM-7550 IOs on J4 (USB 1.1 and 2.0)
2025-09-17 Layout -- WIP...
2025-09-24 Add symbol and footprint for TI TPS25751 -- USB Type-C PD Controller
2025-09-27 Revert "Add symbol and footprint for TI TPS25751 -- USB Type-C PD Controller"
    Another PD controller will be used instead.
    This reverts commit 4d805ddc3812accc94c9496ae357a3b6832bdf56.
2025-09-28 Replace TI and ST Micro parts in the project library with On Semi counterparts
2025-10-01 USB Power Delivery redesign (STmicro controller is NRND)
2025-10-04 Layout WIP: split power plane (internal layer 2)
2025-10-08 Layout [almost] complete -- all connections are routed
2025-10-11 Final touches -- revision 1.0 schematic is released
2025-10-16 Final touches to the PCB, get ready to generate manufacturing files
2025-10-16 PCB production and assembly files
2025-10-16 Update README.md with USB 3 Adapter ready for produciton
2025-10-16 KiCad render of USB3 Adapter board ready for production
2025-10-16 Fix release date on the schematic title sheet and add a link to the schematic from README
2026-01-17 Add an image of the USB 3 Adapter board
